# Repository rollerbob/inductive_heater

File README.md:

# Индукционный нагреватель
_05.2020_  
RollerBob  
***
Простейший индукционный нагреватель.  
Наревательный контур изготовлен из медного провода диаметром 3-5 мм, 10 витков с отводом от середины.

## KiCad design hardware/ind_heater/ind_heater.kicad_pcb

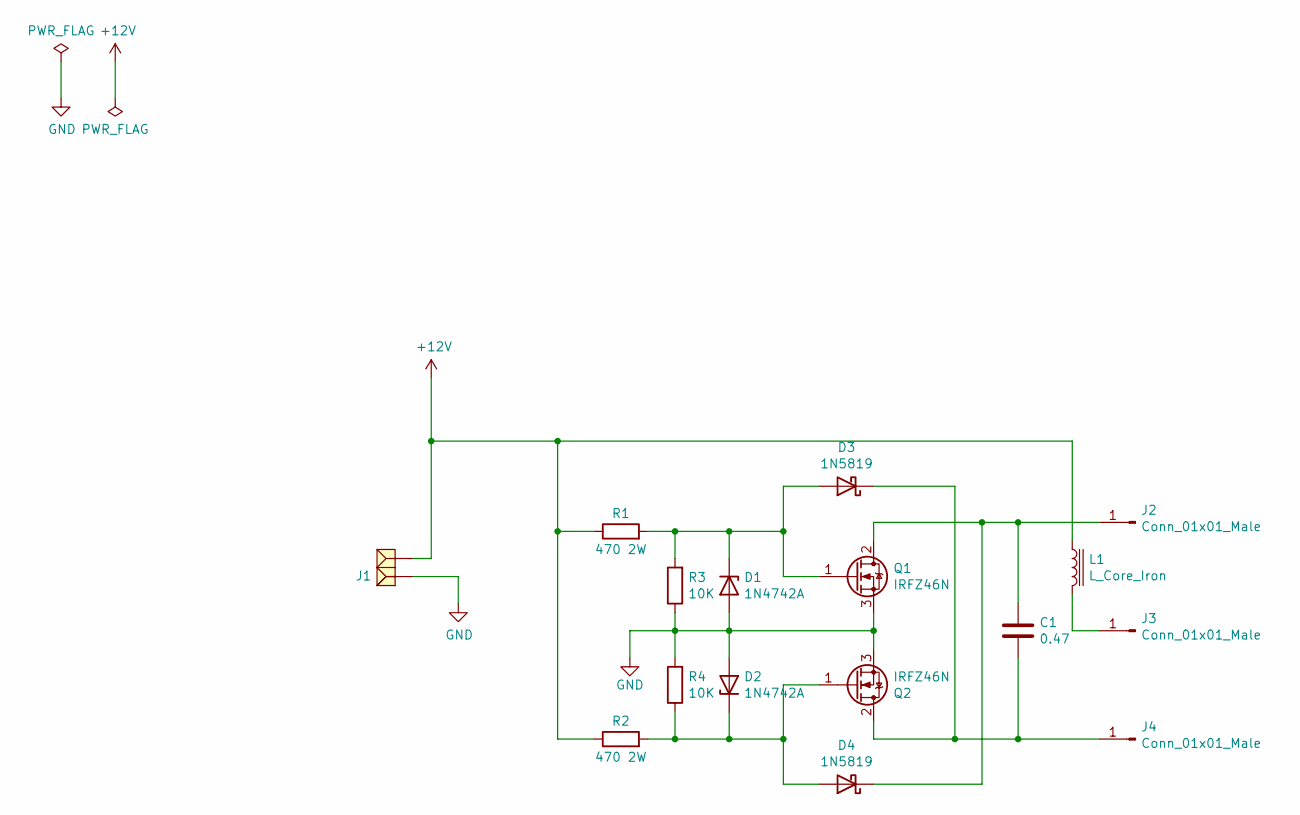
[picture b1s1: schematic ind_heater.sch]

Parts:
C1: 0.47; C_Rect_L41.5mm_W17.0mm_P37.50mm_MKS4
D1, D2: 1N4742A; D_DO-41_SOD81_P10.16mm_Horizontal
D3, D4: 1N5819; D_DO-41_SOD81_P10.16mm_Horizontal
J1: DG126-5.0-02P; DG125-5.0-02P
J2, J3, J4: Conn_01x01_Male; Pin_D1.0mm_L10.0mm_LooseFit
L1: L_Core_Iron; L_Toroid_Vertical_L21.6mm_W9.1mm_P8.40mm_Bourns_5700
Q1, Q2: IRFZ46N; TO-220-3_Vertical
R1, R2: 470 2W; R_Axial_DIN0411_L9.9mm_D3.6mm_P25.40mm_Horizontal
R3, R4: 10K; R_Axial_DIN0204_L3.6mm_D1.6mm_P2.54mm_Vertical

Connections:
+12V: J1.2, L1.1, R1.1, R2.1
GND: D1.2 (A), D2.2 (A), J1.1, Q1.3 (S), Q2.3 (S), R3.1, R4.2
unnamed: C1.1, D4.1 (K), J2.1, Q1.2 (D)
unnamed: C1.2, D3.1 (K), J4.1, Q2.2 (D)
unnamed: D1.1 (K), D3.2 (A), Q1.1 (G), R1.2, R3.2
unnamed: D2.1 (K), D4.2 (A), Q2.1 (G), R2.2, R4.1
unnamed: J3.1, L1.2

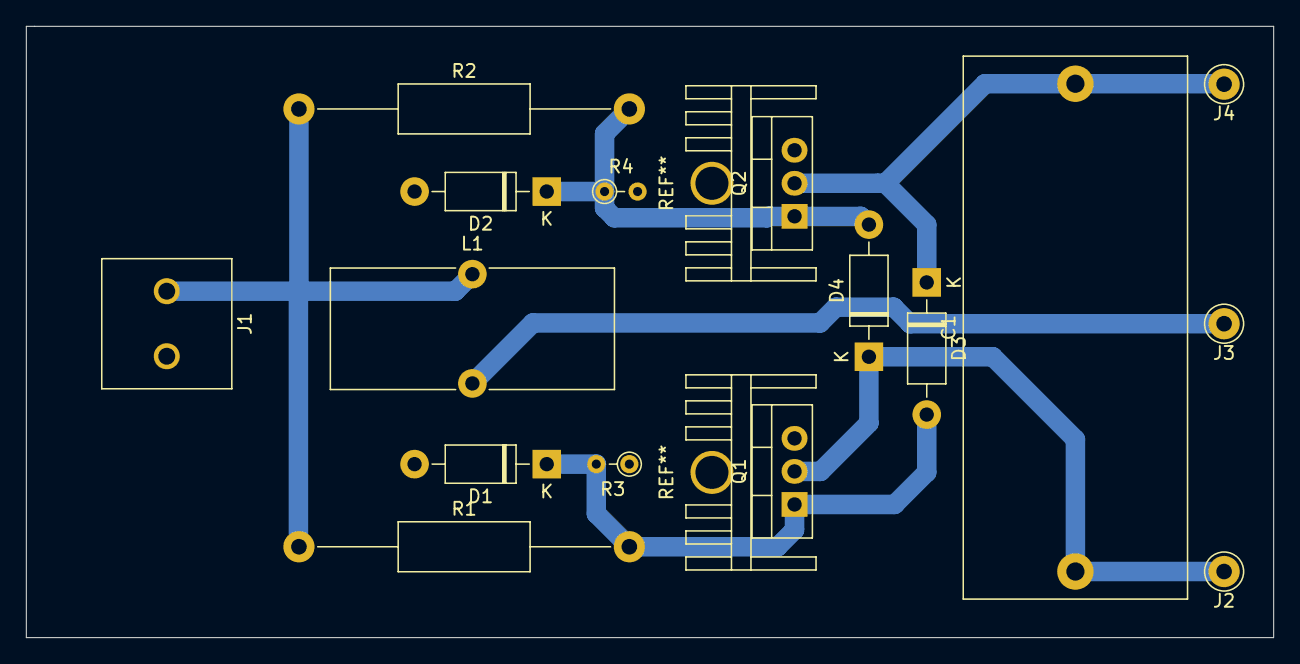
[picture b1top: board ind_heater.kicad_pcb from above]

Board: 2 copper layers, 95.9 x 47.0 mm, 16 parts (0 on the bottom side), 7 nets.

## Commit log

2020-05-03 readme edited
2020-06-05 gitignore added
2020-06-05 тестовая плата собрана, но не проверена
